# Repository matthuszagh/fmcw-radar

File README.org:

This repo has been moved to [[https://github.com/matthuszagh/fmcw][fmcw]] to support git-lfs (public forks do not support LFS).

* About
:PROPERTIES:
:ID:       20ff1c28-cfc6-4280-8501-83314fee390d
:END:
This repo includes the custom PCBs and PC control software necessary
to build and operate a 6GHz FMCW radar. It also includes a number of
other useful additions, such as RF and SPICE simulations (in progress)
as well as CAD designs for the horn antennas and PCB cases.

The project is a fork of [[https://github.com/Ttl/fmcw3][Henrik's excellent design]]. Although I've made
a number of [[id:8f78da8c-ec0c-40f3-9b8b-6c1af11f4bb2][significant changes]], most of the main PCB (as of this
writing) is still identical to Henrik's. Despite the fact that Henrik
deserves a large share of the credit for this project, he is in no way
affiliated with this fork.

This project is still in its early stages. In particular, there are a
number of hardware issues that make this version inferior to
Henrik's. These will be fixed in a future version, but I would hold
off building this version until these issues are fixed.

* TODO Capabilites
Briefly mention the radar's capabilities.

* TODO Installation
* TODO Additional hardware
* Modifications from the original
:PROPERTIES:
:ID:       8f78da8c-ec0c-40f3-9b8b-6c1af11f4bb2
:END:
The FPGA code has been completely rewritten and expanded so that
nearly all data processing is now done on the FPGA. This was done
while keeping the same FPGA chip. This allows the fully processed
output to be plotted in realtime and simplifies the data processing
requirements of the host PC code. The FPGA code also includes
automated tests and, in some cases, formal verification.

Because the FPGA responsibilities were expanded, the PC software had
new requirements and had to be rewritten as well. The software is
multithreaded and separates out the task of acquiring data from
plotting it. Additionally, the software and FPGA gateware have been
designed to make the radar easier to debug. For instance, data
processing can be shared in any way between the software and FPGA,
which makes gateware bugs easier to isolate. It's also possible to
request data from the FPGA in any intermediate form.

I completely redid the PCB layout because of the need for a new power
amplifier (note that this introduced at least [[id:0246fbe1-ba4a-4bf6-b551-a896264dea3a][one significant issue]]).

I've added horn antennas that can be built by anyone with access to a
3D printer. There's also a 3D-printable mount to hold the entire
structure.

I've greatly expanded the documentation, which should be useful to
anyone who wants to understand how the radar works in detail.

I've added a number of RF simulations (using [[https://openems.de/start/][OpenEMS]]) and spice
simulations (using [[http://ngspice.sourceforge.net/][Ngspice]]).

Finally, I have plans to multiplex 8 receiver antennas across the 2
receiver channels for better angular resolution. The PCB has already
been built (though is untested), but I haven't yet had the time to
write the FPGA code and software to support it.

* Issues and To-Do
:PROPERTIES:
:ID:       0246fbe1-ba4a-4bf6-b551-a896264dea3a
:END:
The power circuitry that was added to accommodate a new power
amplifier (the original was deprecated) adds noise that shows up in
the final output. Because of this problem, if you're able to track
down the old power amplifier I'd recommend using Henrik's design
instead. My FPGA code and software (at least for now) should be fully
compatible with the original hardware. I intend to fix this problem in
a future version.

I'm currently working on a number of RF simulations that will
eventually lead to a replacement of some of the RF PCB
layout. Currently, I have very limited information on whether these
parts of the PCB actually work the way they should. Areas of focus
include transmission line characteristic impedance, transmission line
to SMA transitions, and replacement of discrete components such as
couplers, attenuators, etc. with the equivalent components etched
directly onto the PCB. Once the RF simulations are complete, I'd like
to prototype these before actually building them into the
radar. Unfortunately, I don't yet have the proper testing equipment
for this (building a VNA is the next project...).

* Contributing
Pull requests and issues welcome. I'm open to suggestions for hardware
modification, although may or may not be able to merge those commits
depending on whether I can test the change.

* TODO Operation
Link blog post.

* TODO Attribution
+ Henrik, of course (see [[id:20ff1c28-cfc6-4280-8501-83314fee390d][About]]).
+ An additional thanks to AlexBdx for finding a way to 3D print horn
  antennas.

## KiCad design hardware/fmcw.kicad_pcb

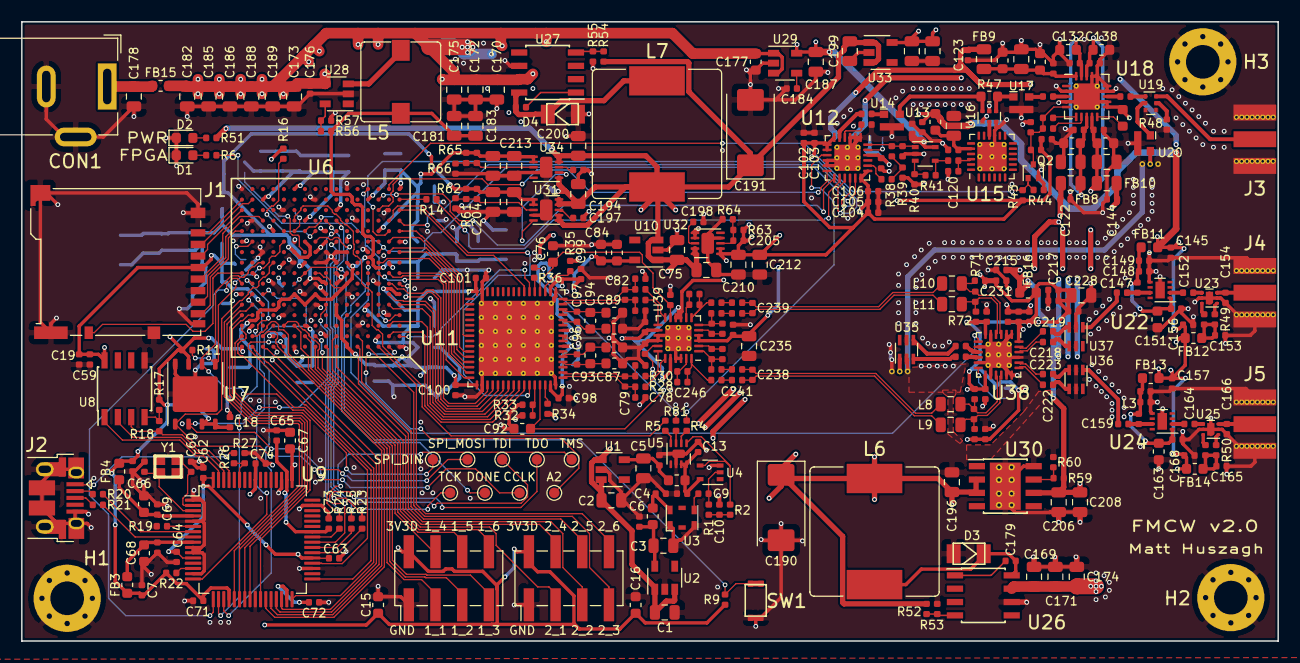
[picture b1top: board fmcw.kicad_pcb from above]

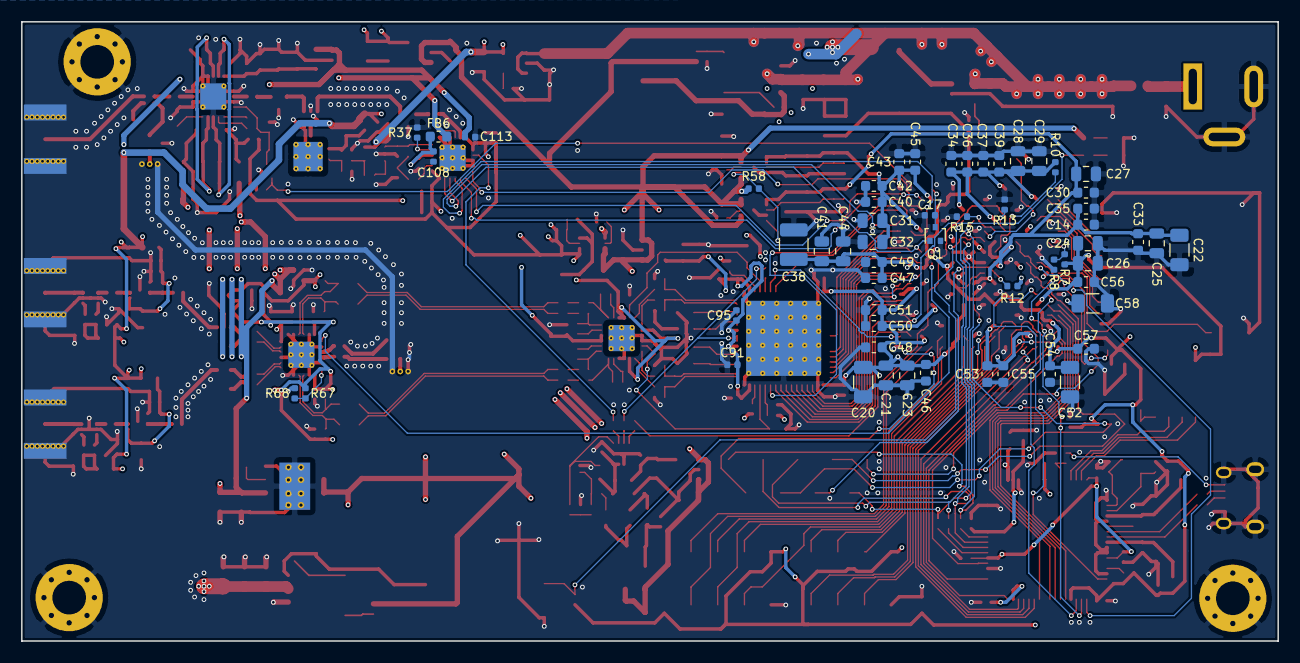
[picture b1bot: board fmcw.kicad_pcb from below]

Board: 4 copper layers, 119.6 x 58.9 mm, 412 parts (57 on the bottom side), 247 nets.

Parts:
C1, C2, C3, C5, C75, C118, C129, C133, C139, C169, C170, C171, C172, C173, C174, C175, C178, C181, C182, C183, C187, C194, C195, C196, C199, C200, C201, C206, C207, C210, C213, C228: 10u; C_0805_2012Metric
C4, C9, C10, C119, C149, C161, C179, C180, C184, C204, C205, C211, C240, C241, C242, C243: 10n; C_0402_1005Metric
C6, C7, C8, C11, C12, C13, C18, C19, C59, C62, C63, C64, C65, C69, C70, C71, C72, C73, C74, C91, C95, C96, C97, C98, C99, C100, C101, C102, C104, C105, C108, C113, C115, C116, C121, C122, C123, C144, C145, C153, C156, C157, C165, C168, C176, C197, C198, C203, C215, C216, C217, C224, C229, C230, C231, C232, C233, C234, C244, C245: 100n; C_0402_1005Metric
C14, C15, C16, C30, C33, C34, C35, C36, C37, C39, C40, C42, C43, C45, C46, C47, C48, C49, C50, C51, C53, C54, C55, C56, C57: 470n; C_0603_1608Metric
C17, C236, C237: DNP; C_0402_1005Metric
C20, C22, C52, C58: 47u; C_1206_3216Metric
C21, C23, C24, C25, C26, C27, C28, C29, C31, C32, C41, C44: 4.7u; C_0805_2012Metric
C38: 100u; C_1210_3225Metric
C60, C61: 15p; C_0402_1005Metric
C66, C67, C68: 4.7u; C_0603_1608Metric
C76, C92, C93, C94, C130, C134, C140: 2.2u; C_0603_1608Metric
C77, C84, C87, C88, C89, C90, C177: 1u; C_0603_1608Metric
C78, C79, C80, C81, C82, C83, C131, C135, C136, C141, C142, C150, C162, C225, C226, C227: 100p; C_0402_1005Metric
C103, C106, C107, C109, C112, C124, C127, C148, C160, C246, C247, C248, C249, C251, C252: 10p; C_0402_1005Metric
C110, C238, C239: 2.2n; C_0402_1005Metric
C114: 51p; C_0402_1005Metric
C120: 68p; C_0402_1005Metric
C128, C132, C137, C138, C151, C163: DNP; C_0603_1608Metric
C147, C152, C159, C164: 18p; C_0402_1005Metric
C154, C166: 0.5p; C_0402_1005Metric
C185, C186, C188, C189, C202, C208, C209, C212, C214, C235: DNP; C_0805_2012Metric
C190, C191: 100u; CP_EIA-7343-31_Kemet-D
C218, C219, C220, C221, C222, C223: 3p; C_0402_1005Metric
CON1: BARREL_JACK; BarrelJack_Wuerth_6941xx301002
D1, D2: Red; LED_0603_1608Metric
D3, D4: SS24FL; SOD-123F
F1, F2: Via-fmcw3-rescue; RF_via
FB1, FB2, FB3, FB4, FB6, FB7, FB11, FB12, FB13, FB14, FB16: BLM18PG181SH1D; L_0603_1608Metric
FB8, FB9, FB10: CIC21P101NE; L_0805_2012Metric
FB15: 74279228600; L_0603_1608Metric
H1, H2, H3: MountingHole_Pad; MountingHole_3.2mm_M3_Pad_Via
J1: SD_Card; microSD_HC_Hirose_DM3BT-DSF-PEJS
J2: USB_B_Micro; USB_Micro-B_Amphenol_10103594-0001LF_Horizontal
J3, J4, J5: SMA; CONSMA003.062
L1, L3: LQW15AN9N9J80D; L_0402_1005Metric
L2, L4: 0.6n; L_0402_1005Metric
L5: 10u; L_Wuerth_WE-PD-Typ-7345
L6, L7: 33u; L_Bourns_SRR1210A
L8, L9, L10, L11: 2.2u; L_0805_2012Metric
P1, P2: CONN_02X04; PinHeader_2x04_P2.54mm_Vertical_SMD
Q1: DNP(RE1C002UN); SOT-416
Q2: RE1C002UN; SOT-416
R1, R2: 470k; R_0402_1005Metric
R4, R5, R14, R23, R24, R25, R81: 33; R_0402_1005Metric
R6, R51: 240; R_0402_1005Metric
R7, R16, R33, R38, R44, R68: DNP; R_0402_1005Metric
R8, R13, R15, R20, R21, R32, R34, R35: 0; R_0402_1005Metric
R9, R10, R11, R26, R40, R41, R42: 4.7k; R_0402_1005Metric
R12, R22: 1k; R_0402_1005Metric
R17, R27, R46, R52, R54: 10k; R_0402_1005Metric
R18: 2.2k; R_0402_1005Metric
R19: 12k; R_0402_1005Metric
R28, R29, R30, R31, R48, R69, R70, R71, R72: 49.9; R_0402_1005Metric
R36: 22; R_0402_1005Metric
R37: 5.49k; R_0402_1005Metric
R39: 3.09k; R_0402_1005Metric
R43: 47k; R_0402_1005Metric
R45, R62: 1.5k; R_0402_1005Metric
R47: 100; R_0603_1608Metric
R49, R50: 100; R_0402_1005Metric
R53: 2.8k; R_0402_1005Metric
R55: 5.11k; R_0402_1005Metric
R56: 4.99k; R_0402_1005Metric
R57: 20k; R_0402_1005Metric
R58: 68k; R_0402_1005Metric
R59: 274k; R_0402_1005Metric
R60: 30.1k; R_0402_1005Metric
R61: 1.87k; R_0402_1005Metric
R63, R65: 3.57k; R_0402_1005Metric
R64, R66: 1.15k; R_0402_1005Metric
R67: 2k; R_0402_1005Metric
R73, R74, R75, R76: 549; R_0402_1005Metric
R77, R78, R79, R80: 8.2k; R_0402_1005Metric
SW1: SW_PUSH; EVP-AWBA2A
TP1, TP2, TP3, TP4, TP5, TP6, TP7, TP8, TP9: TestPoint; TestPoint_Pad_D1.0mm
U1: LP5907MFX-3.3; SOT-23-5
U2: LP5907MFX-1.8; SOT-23-5
U3: KT2520K-T; Oscillator_SMD_Kyocera_2520-6Pin_2.5x2.0mm
U4: NC7SVU04P5X; SOT-353_SC-70-5
U5: NB3N551; DFN-8-1EP_2x2mm_P0.5mm_EP0.8x1.2mm
U6: XC7A15T-FTG256; FTG256
U7: W25Q32JV; DFN-8-1EP_6x5mm_P1.27mm_EP3.4x4.3mm
U8: 93LCxxB; SOIC-8_3.9x4.9mm_P1.27mm
U9: FT2232H; LQFP-64_10x10mm_P0.5mm
U10, U33: LP5907MFX-3.0; SOT-23-5
U11: LTC2292; QFN-64-1EP_9x9mm_P0.5mm_EP7.15x7.15mm_ThermalVias
U12: ADF4158; LFCSP-24-1EP_4x4mm_P0.5mm_EP2.5x2.5mm_ThermalVias
U13: TLV172DCK; SOT-353_SC-70-5
U14: PAT1220-3dB; RF_Attenuator_Susumu_PAT1220
U15: HMC431LP4; QFN-24-1EP_4x4mm_P0.5mm_EP2.8x2.8mm_ThermalVias
U16: PD4859J5050S2HF; Anaren_0805_2012Metric-6
U17: PAT1220-5dB; RF_Attenuator_Susumu_PAT1220
U18: SE5004L; QFN-20-1EP_4x4mm_P0.5mm_EP2.5x2.5mm_ThermalVias
U19: DC4759J5020AHF; Anaren_0805_2012Metric-6
U20: PAT1220-6dB; RF_Attenuator_Susumu_PAT1220
U22, U24: TRF37A73; WSON-8-1EP_2x2mm_P0.5mm_EP0.9x1.6mm
U23, U25: SKY65404; Skyworks_DFN-6-1EP_1.5x1.5mm_P0.5mm_EP0.7x1.2mm
U26, U27: TPS5420D; SOIC-8_3.9x4.9mm_P1.27mm
U28: TPS560200; SOT-23-5
U29: LP2985A-10DBVR; SOT-23-5
U30: TPS7A7001DDA; TI_SO-PowerPAD-8_ThermalVias
U31, U32, U34: TPS7A91; DFN-10-1EP_2.5x2.5mm_P0.5mm_EP1.2x2mm
U35, U36, U37: 5400BL15B050E; Balun_Johanson_5400BL15B050E
U38: ADL5802; LFCSP-24-1EP_4x4mm_P0.5mm_EP2.5x2.5mm_ThermalVias
U39: ADA4940-2; LFCSP-24-1EP_4x4mm_P0.5mm_EP2.5x2.5mm_ThermalVias
Y1: 12MHz; ABM10

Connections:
/1V0: C38.1, C41.1, C44.1, C47.1, C49.1, C52.1, C54.1, C181.1, C183.1, L5.2, R56.1, U6.E10, U6.F7, U6.F9, U6.F11, U6.G6, U6.H9, U6.J6, U6.K9, U6.L8
/1V8: C14.2, C22.1, C25.1, C27.1, C30.1, C33.1, C35.1, C204.1, C207.1, C209.1, R61.1, U6.G8, U6.G10, U6.J10, U6.K11, U6.L10, U31.1, U31.2
/1V8_OSC: C3.1, C6.1, FB1.2, U2.5
/3V0: C116.1, C145.1, C156.1, C157.1, C168.1, C201.1, C202.1, FB7.2, FB11.2, FB12.2, FB13.2, FB14.2, U33.5
/3V3A: C102.1, C103.1, C104.1, C105.1, C106.1, C121.1, C205.1, C210.1, C212.1, C233.1, C234.1, C235.1, R43.1, R45.1, R63.1, U12.6, U12.7, U12.8, U12.18, U12.19, U32.1, U32.2, U39.3, U39.4, U39.9, U39.10, U39.14, U39.20
/3V3D: C7.1, C8.1, C15.1, C16.1, C18.2, C19.1, C20.1, C21.1, C23.1, C24.1, C26.1, C28.1, C29.1, C31.1, C32.1, C34.1, C36.1, C37.1, C39.1, C40.1, C42.1, C43.1, C45.1, C46.1, C48.1, C50.1, C51.1, C53.1, C55.1, C56.1, C57.1, C58.1, C59.1, C65.2, C71.1, C72.1, C73.1, C74.1, C100.1, C101.1, C211.1, C213.1, C214.1, FB3.2, FB4.1, J1.4, P1.2, P2.2, R7.1, R9.1, R10.1, R11.1, R12.1, R16.1, R17.1, R22.2, R65.1, U6.A6, U6.A16, U6.B3, U6.B13, U6.C10, U6.D7, U6.E4, U6.E7, U6.E14, U6.F1, U6.H15, U6.J2, U6.J12, U6.L6, U6.L16, U6.M3, U6.M13, U6.N10, U6.P7, U6.R4, U6.R14, U6.T1, U6.T11, U7.3, U7.7, U7.8, U8.8, U9.20, U9.31, U9.42, U9.50, U9.56, U11.32, U11.49, U34.1, U34.2
/3V3_INV: C5.1, C12.1, FB2.2, U1.5
/3V6: C1.1, C2.1, C75.1, C191.1, C194.1, C195.1, C199.1, C200.1, L7.2, R51.1, R54.1, R58.1, U1.1, U1.3, U2.1, U2.3, U10.1, U10.3, U31.6, U31.7, U31.9, U31.10, U32.6, U32.7, U32.9, U32.10, U33.1, U33.3, U34.6, U34.9, U34.10
/5V: C113.1, C122.1, C123.1, C144.1, C206.1, C208.1, C215.2, FB6.2, FB8.2, FB9.2, FB10.1, FB16.2, R59.1, U30.6
/10V: C115.2, C187.1, U13.5, U29.5
/ADC1+: R31.2, U39.13
/ADC1-: R29.2, U39.12
/ADC2+: R30.2, U39.18
/ADC2-: R28.2, U39.19
/ADC_CE: U6.R3, U12.13
/ADC_REF: R36.2, R81.1, U11.8, U11.9
/ADC_VCM1: C92.2, C244.1, U11.61, U39.17
/ADC_VCM2: C76.1, C245.1, U11.20, U39.11
/ADF_CLK: R14.2, U12.14
/ADF_DATA: U6.M2, U12.15
/ADF_LE: U6.N1, U12.16
/ADF_MUXOUT: Q1.1, U6.K3, U12.17
/ADF_REF: R4.1, U12.9
/ADF_TXDATA: U6.P3, U12.12
/FPGA_REF: R5.1, U6.N11
/LO: F1.1, F2.1, U20.2, U35.1
/MIX_ENBL: U6.J4, U38.7
/PA_OFF: Q2.1, R43.2, R44.1, U6.T2
/RF1: C147.2, U37.1
/RF2: C159.2, U36.1
/fpga/ADC_OE1: U6.B2, U11.58
/fpga/ADC_OE2: U6.P1, U11.23
/fpga/ADC_SHDN1: U6.B1, U11.22
/fpga/ADC_SHDN2: U6.N2, U11.59
/fpga/ADF_DONE: C17.1, Q1.3, U6.T4
/fpga/CARD_DETECT: J1.10, U6.H16
/fpga/CCLK: TP8.1, U6.E8, U7.6
/fpga/CLKOUT: U6.A15, U9.32
/fpga/D0: U6.L2, U11.43
/fpga/D1: U6.K2, U11.44
/fpga/D2: U6.K1, U11.45
/fpga/D3: U6.J3, U11.46
/fpga/D4: U6.H1, U11.47
/fpga/D5: U6.H2, U11.48
/fpga/D6: U6.H3, U11.51
/fpga/D7: U6.G2, U11.52
/fpga/D8: U6.G1, U11.53
/fpga/D9: U6.F2, U11.54
/fpga/D10: U6.E1, U11.55
/fpga/D11: U6.E2, U11.56
/fpga/EXT1_1: P1.3, U6.C11
/fpga/EXT1_2: P1.5, U6.B10
/fpga/EXT1_3: P1.7, U6.A9
/fpga/EXT1_4: P1.4, U6.C12
/fpga/EXT1_5: P1.6, U6.B9
/fpga/EXT1_6: P1.8, U6.A8
/fpga/EXT2_1: P2.3, U6.B7
/fpga/EXT2_2: P2.5, U6.A5
/fpga/EXT2_3: P2.7, U6.A4
/fpga/EXT2_4: P2.4, U6.A7
/fpga/EXT2_5: P2.6, U6.B5
/fpga/EXT2_6: P2.8, U6.A3
/fpga/FT_D0: U6.F15, U9.16
/fpga/FT_D1: U6.G16, U9.17
/fpga/FT_D2: U6.G15, U9.18
/fpga/FT_D3: U6.F14, U9.19
/fpga/FT_D4: U6.E16, U9.21
/fpga/FT_D5: U6.E15, U9.22
/fpga/FT_D6: U6.D16, U9.23
/fpga/FT_D7: U6.D15, U9.24
/fpga/FT_SUSPEND: U6.C16, U9.36
/fpga/INIT_B: R10.2, U6.K10
/fpga/LED: R6.1, U6.D1
/fpga/M0: R16.2, U6.M9
/fpga/M1: R15.1, U6.M10
/fpga/M2: R13.1, U6.M11
/fpga/OE#: U6.A12, U9.33
/fpga/OF1: U6.C2, U11.57
/fpga/OF2: U6.M1, U11.40
/fpga/PROGRAM_B: R9.2, SW1.1, U6.L9
/fpga/RD#: U6.B14, U9.28
/fpga/RXF#: U6.B16, U9.26
/fpga/SD_CLK: J1.5, U6.N14
/fpga/SD_CMD: J1.3, U6.P16
/fpga/SD_DAT0: J1.7, U6.N16
/fpga/SD_DAT1: J1.8, U6.M16
/fpga/SD_DAT2: J1.1, U6.R16
/fpga/SD_DAT3: J1.2, U6.R15
/fpga/SIWUA: U6.A13, U9.30
/fpga/SPI_CS: R11.2, U6.L12, U7.1
/fpga/SPI_DIN: TP1.1, U6.J14, U7.2
/fpga/SPI_MOSI: TP2.1, U6.J13, U7.5
/fpga/TCK: R23.1, TP6.1, U6.L7
/fpga/TDI: R25.1, TP3.1, U6.N7
/fpga/TDO: TP4.1, U6.N8, U9.40
/fpga/TMS: R24.1, TP5.1, U6.M7
/fpga/TXE#: U6.B15, U9.27
/fpga/WR: U6.A14, U9.29
/fpga/adc/3V0: R32.1, R34.2, R35.2
/fpga/adc/AINA+: C78.2, C79.1, R28.1, U11.1
/fpga/adc/AINA-: C79.2, C80.1, R30.1, U11.2
/fpga/adc/AINB+: C81.2, C82.1, R29.1, U11.16
/fpga/adc/AINB-: C82.2, C83.1, R31.1, U11.15
/fpga/usb/1V8: C62.1, C63.1, C64.1, C67.1, U9.12, U9.37, U9.49, U9.64
/fpga/usb/DO: R17.2, R18.1, U8.4
/fpga/usb/EECLK: U8.2, U9.62
/fpga/usb/EECS: U8.1, U9.63
/fpga/usb/EEDATA: R18.2, U8.3, U9.61
/fpga/usb/USBDM: J2.2, R20.2
/fpga/usb/USBDP: J2.3, R21.2
/fpga/usb/USB_5V: J2.1, R26.1
/if/IF1+: C237.2, L11.1, R72.2, U38.4
/if/IF1-: C237.1, L10.1, R71.1, U38.3
/if/IF1a+: C239.2, C243.2, L11.2
/if/IF1a-: C239.1, C242.2, L10.2
/if/IF1b+: C243.1, R76.2
/if/IF1b-: C242.1, R75.2
/if/IF2+: C236.2, L9.1, R70.2, U38.16
/if/IF2-: C236.1, L8.1, R69.1, U38.15
/if/IF2a+: C238.2, C241.2, L9.2
/if/IF2a-: C238.1, C240.2, L8.2
/if/IF2b+: C241.1, R74.2
/if/IF2b-: C240.1, R73.2
/mixer/5VF: C216.2, C217.2, C224.2, C225.2, C226.2, C227.2, C228.2, C229.2, C230.2, C231.2, C232.2, FB16.1, R67.1, R69.2, R70.1, R71.2, R72.1, U38.6, U38.13, U38.24
/mixer/LOIa+: C220.2, U35.4
/mixer/LOIa-: C221.2, U35.3
/mixer/LOIb+: C220.1, U38.9
/mixer/LOIb-: C221.1, U38.10
/mixer/RF1a+: C219.2, U37.3
/mixer/RF1a-: C218.2, U37.4
/mixer/RF1b+: C219.1, U38.23
/mixer/RF1b-: C218.1, U38.22
/mixer/RF2a+: C223.2, U36.3
/mixer/RF2a-: C222.2, U36.4
/mixer/RF2b+: C223.1, U38.20
/mixer/RF2b-: C222.1, U38.19
/power/5V6: C190.1, C196.1, L6.2, R52.1, U30.2, U30.3
/power/12V: C169.1, C170.1, C171.1, C172.1, C173.1, C174.1, C175.1, C176.1, C177.1, C182.1, C185.1, C186.1, C188.1, C189.1, FB15.1, U26.7, U27.7, U28.4, U29.1, U29.3
GND: C1.2, C2.2, C3.2, C4.1, C5.2, C6.2, C7.2, C8.2, C10.1, C11.1, C12.2, C13.1, C14.1, C15.2, C16.2, C17.2, C18.1, C19.2, C20.2, C21.2, C22.2, C23.2, C24.2, C25.2, C26.2, C27.2, C28.2, C29.2, C30.2, C31.2, C32.2, C33.2, C34.2, C35.2, C36.2, C37.2, C38.2, C39.2, C40.2, C41.2, C42.2, C43.2, C44.2, C45.2, C46.2, C47.2, C48.2, C49.2, C50.2, C51.2, C52.2, C53.2, C54.2, C55.2, C56.2, C57.2, C58.2, C59.2, C60.2, C61.2, C62.2, C63.2, C64.2, C65.1, C66.2, C67.2, C68.2, C69.2, C70.2, C71.2, C72.2, C73.2, C74.2, C75.2, C76.2, C77.2, C78.1, C80.2, C81.1, C83.2, C84.2, C87.2, C88.2, C89.2, C90.2, C91.2, C92.1, C95.2, C98.2, C99.2, C100.2, C101.2, C102.2, C103.2, C104.2, C105.2, C106.2, C107.1, C108.2, C109.2, C113.2, C114.2, C115.1, C116.2, C118.1, C119.1, C120.2, C121.2, C122.2, C123.2, C128.2, C129.2, C130.2, C131.2, C132.1, C133.1, C134.1, C135.1, C136.1, C137.2, C138.1, C139.1, C140.1, C141.1, C142.1, C144.2, C145.2, C148.2, C149.2, C150.2, C151.2, C153.2, C154.2, C156.2, C157.2, C160.2, C161.2, C162.2, C163.2, C165.2, C166.2, C168.2, C169.2, C170.2, C171.2, C172.2, C173.2, C174.2, C175.2, C176.2, C177.2, C178.2, C181.2, C182.2, C183.2, C184.2, C185.2, C186.2, C187.2, C188.2, C189.2, C190.2, C191.2, C194.2, C195.2, C196.2, C197.2, C198.2, C199.2, C200.2, C201.2, C202.2, C203.2, C206.2, C207.2, C208.2, C209.2, C210.2, C212.2, C213.2, C214.2, C215.1, C216.1, C217.1, C224.1, C225.1, C226.1, C227.1, C228.1, C229.1, C230.1, C231.1, C232.1, C233.2, C234.2, C235.2, C244.2, C245.2, CON1.2, CON1.3, D1.1, D2.1, D3.2, D4.2, F1.2, F2.2, H1.1, H2.1, H3.1, J1.6, J1.9, J1.11, J2.5, J2.6, J3.2, J4.2, J5.2, P1.1, P2.1, Q1.2, Q2.2, R8.2, R13.2, R15.2, R19.2, R27.2, R33.2, R37.2, R39.1, R40.2, R44.2, R46.2, R48.1, R53.2, R55.2, R57.2, R60.2, R62.2, R64.2, R66.2, R68.2, SW1.2, U1.2, U2.2, U3.1, U3.3, U4.3, U5.6, U5.9, U6.A1, U6.A11, U6.B8, U6.C5, U6.C15, U6.D2, U6.D12, U6.E9, U6.F6, U6.F8, U6.F10, U6.F16, U6.G3, U6.G7, U6.G9, U6.G13, U6.H6, U6.H7, U6.J7, U6.J8, U6.J9, U6.J11, U6.K4, U6.K6, U6.K7, U6.K8, U6.K14, U6.L1, U6.L11, U6.M8, U6.N5, U6.N15, U6.P2, U6.P12, U6.R9, U6.T6, U6.T16, U7.4, U7.9, U8.5, U9.1, U9.5, U9.10, U9.11, U9.13, U9.15, U9.25, U9.35, U9.47, U9.51, U10.2, U11.17, U11.31, U11.50, U11.64, U11.65, U12.1, U12.2, U12.3, U12.10, U12.11, U12.25, U13.2, U14.3, U15.15, U15.25, U16.1, U16.3, U16.5, U17.3, U18.2, U18.4, U18.11, U18.12, U18.14, U18.15, U18.16, U18.17, U18.21, U19.3, U19.4, U20.3, U22.5, U22.9, U23.2, U23.5, U23.7, U24.5, U24.9, U25.2, U25.5, U25.7, U26.6, U27.6, U28.2, U29.2, U30.8, U30.9, U31.4, U31.11, U32.4, U32.11, U33.2, U34.4, U34.11, U35.2, U35.5, U36.2, U36.5, U37.2, U37.5, U38.1, U38.2, U38.5, U38.8, U38.11, U38.14, U38.17, U38.18, U38.21, U38.25, U39.15, U39.16, U39.21, U39.22, U39.25
unnamed: C4.2, FB1.1, U3.6
unnamed: C9.1, R1.2, U4.2
unnamed: C9.2, U3.4
unnamed: C10.2, R1.1, R2.2
unnamed: C11.2, C13.2, FB2.1, U4.5, U5.7, U5.8
unnamed: C60.1, U9.2, Y1.1
unnamed: C61.1, U9.3, Y1.3
unnamed: C66.1, C69.1, FB4.2, U9.4
unnamed: C68.1, C70.1, FB3.1, U9.9
unnamed: C77.1, C84.1, C91.1, C95.1, C98.1, C99.1, U10.5, U11.7, U11.10, U11.18, U11.63
unnamed: C87.1, C93.1, C96.1, U11.3, U11.4
unnamed: C88.1, C93.2, C96.2, U11.5, U11.6
unnamed: C89.1, C94.1, C97.1, U11.13, U11.14
unnamed: C90.1, C94.2, C97.2, U11.11, U11.12
unnamed: C107.2, U12.4
unnamed: C108.1, C109.1, FB6.1, U12.22
unnamed: C110.1, C114.1, U12.24, U13.1
unnamed: C110.2, R38.1, R39.2
unnamed: C112.1, U14.1
unnamed: C112.2, U12.5
unnamed: C118.2, C119.2, FB7.1, U15.20
unnamed: C120.1, R42.1, U15.22
unnamed: C124.1, U18.7
unnamed: C124.2, C127.2, Q2.3, R45.2, R46.1, U18.5
unnamed: C127.1, U18.6
unnamed: C128.1, C129.1, C130.1, C131.1, FB9.1, U18.20
unnamed: C132.2, C133.2, C134.2, C135.2, C136.2, FB8.1, U18.8, U18.19
unnamed: C137.1, U18.10
unnamed: C138.2, C139.2, C140.2, C141.2, C142.2, FB10.2, U18.9, U18.18
unnamed: C147.1, L1.1, U22.7
unnamed: C148.1, C149.1, C150.1, C151.1, FB11.1, L1.2, U22.1
unnamed: C152.1, U23.4
unnamed: C152.2, U22.2
unnamed: C153.1, FB12.1, L2.2, R49.2
unnamed: C154.1, J4.1, U23.3
unnamed: C159.1, L3.1, U24.7
unnamed: C160.1, C161.1, C162.1, C163.1, FB13.1, L3.2, U24.1
unnamed: C164.1, U25.4
unnamed: C164.2, U24.2
unnamed: C165.1, FB14.1, L4.2, R50.2
unnamed: C166.1, J5.1, U25.3
unnamed: C178.1, CON1.1, FB15.2
unnamed: C179.1, D3.1, L6.1, U26.8
unnamed: C179.2, U26.1
unnamed: C180.1, D4.1, L7.1, U27.8
unnamed: C180.2, U27.1
unnamed: C184.1, U29.4
unnamed: C197.1, U31.8
unnamed: C198.1, U32.8
unnamed: C203.1, U34.8
unnamed: C204.2, R61.2, R62.1, U31.3
unnamed: C205.2, R63.2, R64.1, U32.3
unnamed: C211.2, R65.2, R66.1, U34.3
unnamed: C246.1, R78.1, U39.23
unnamed: C246.2, R74.1, R78.2, U39.24
unnamed: C247.1, R80.1, U39.5
unnamed: C247.2, R76.1, R80.2, U39.6
unnamed: C248.1, R73.1, R77.1, U39.1
unnamed: C248.2, R77.2, U39.2
unnamed: C249.1, R75.1, R79.1, U39.7
unnamed: C249.2, R79.2, U39.8
unnamed: C251.1, U18.3
unnamed: C251.2, U17.2
unnamed: C252.1, U19.1
unnamed: C252.2, U18.13
unnamed: D1.2, R6.2
unnamed: D2.2, R51.2
unnamed: J3.1, U19.6
unnamed: L2.1, U23.6
unnamed: L4.1, U25.6
unnamed: L5.1, U28.3
unnamed: R2.1, U4.4, U5.1
unnamed: R4.2, U5.2
unnamed: R5.2, U5.4
unnamed: R7.2, R8.1, U6.L15
unnamed: R12.2, TP7.1, U6.H10
unnamed: R14.1, U6.R1
unnamed: R19.1, U9.6
unnamed: R20.1, U9.7
unnamed: R21.1, U9.8
unnamed: R22.1, U9.14
unnamed: R23.2, U9.38
unnamed: R24.2, U9.41
unnamed: R25.2, U9.39
unnamed: R26.2, R27.1, U9.59
unnamed: R32.2, R33.1, U11.60
unnamed: R34.1, U11.62
unnamed: R35.1, U11.19
unnamed: R36.1, U11.21
unnamed: R37.1, U12.23
unnamed: R38.2, U12.20
unnamed: R40.1, R41.2, U13.3
unnamed: R41.1, R42.2, U13.4
unnamed: R47.1, U16.4, U17.1
unnamed: R47.2, U14.2, U16.6
unnamed: R48.2, U19.5
unnamed: R49.1, U23.1
unnamed: R50.1, U25.1
unnamed: R52.2, R53.1, U26.4
unnamed: R54.2, R55.1, U27.4
unnamed: R56.2, R57.1, U28.5
unnamed: R58.2, U31.5, U34.7
unnamed: R59.2, R60.1, U30.7
unnamed: R67.2, R68.1, U38.12
unnamed: R81.2, U5.3
unnamed: TP9.1, U6.A2
unnamed: U15.16, U16.2
unnamed: U19.2, U20.1

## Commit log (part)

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2017-09-27 Fix FPGA programming resistor connections
    M[2:0] were wired incorrectly when I ordered the board. For programming from SPI
    memory M[2:0] should be "001", but I had them wired backwards as "100". I fixed
    it with one jump wire, but here is a proper fix for anyone looking to reproduce
    the design.
2017-09-28 Update blog post link
2018-10-06 Current working version.
2018-10-10 Dropped the 3 from the end of the project name.
2018-12-11 Modularized LaTeX documentation.
2018-12-18 Adjusted power supply for new power amplifier.
2018-12-20 Documentation for TPS5420D buck converter.
2018-12-26 Made some modifications to the power hardware.
2018-12-30 Improved top level documentation.
2019-01-04 Added MFNs to components.
2019-01-08 Improved documentation and added schematics to default libraries.
2019-01-08 Improved tx sheet and corresponding documentation.
2019-01-09 Improved documentation and parts of the schematic.
2019-01-11 Changed components to official libs.
2019-01-12 Finished design, began routing.
2019-01-13 Placed most major components.
2019-01-14 Completed clock placement and routing.
2019-01-15 Place/route for ft2232h.
2019-01-15 Fixed transmission line width.
2019-01-15 Added test points.
2019-01-16 Placed/routed all FPGA external components.
2019-01-16 Better MFNs for RF DC blocking caps.
2019-01-16 Completed transmitter placement/routing.
2019-01-17 Completed receivers.
2019-01-17 Finished placing.
2019-01-17 Passes DRC.
2019-01-17 Completed power plane.
2019-01-17 Replaced relevant footprints for thermal via variety.
2019-01-18 Improved silkscreen appearance.
2019-01-23 Documentation changes.
2019-01-24 Add patch antenna.
2019-01-24 Documentation improvements and spice simulations.
2019-02-02 Filter FPGA code.
2019-02-02 Place ADC logic directly in top level module.
2019-02-10 Finish FPGA code.
2019-02-24 Added Makefiles to facilitate running code. Reorganized code.
2019-02-24 Add buffer amp for power amp reference voltage.
2019-02-27 Improve PCB.
2019-02-28 Add RF antenna switch.
2019-08-10 Unoptimized, working FFT
    This commit is a huge abuse of git, I know...
2019-09-27 Huge, messy commit before I begin replacing FPGA code
2019-10-01 Add beamforming doc
2019-10-01 Move FPGA code to dedicated subdirectories
    This project will have several different
    configurations. There will be at least 2: (1) just
    to calculate range and (2) calculate range and
    angle data.
2019-10-01 Remove test signals from FPGA code
    This commit simply cleans up the FPGA to act as a
    reference point from which to test.
2019-10-02 Move tap address update in FIR
2019-10-02 Source some cores from libdigital repo
    Previously, I had been copying the relevant files
    from libdigital to this project. Therefore, any
    changes needed to be implemented twice. Instead,
    they should be modified once in the libdigital
    repo and then included here.
2019-10-03 Fix FFT data sent to host
2019-10-03 Minor change
2019-10-03 Add C program for reading raw binary data
    This accepts a header+payload format where the
    header is any 4 or 8 bits and the payload can
    consist of any bit sequence corresponding to any
    sequence of data points (they do not need to be
    byte-aligned). The total header+payload must be
    byte-aligned.
2019-10-04 Eliminate most errors related to missed or erroneous reads
    There still might be a few errors here, but not many.
2019-10-04 Add linker flags to Makefile for reading bytes from fmcw board
2019-10-04 Add code to compute FFT magnitude and generate file
2019-10-04 Update Python plotting
2019-10-04 Add files to gitignore
2019-10-04 Add nix shell file for reproducible environments
2019-10-05 read_bytes: Add numerous payloads for different output data
2019-10-05 Fix FFT power computation when reading bytes
2019-10-05 Add functions to plot file
2019-10-05 Use 40 clk input for all 4 derived clocks
    This also requires a synchronization register at
    the output.
2019-10-06 Add facility to measure error detection method efficacy
2019-10-06 Replace adc.v with ltc2292.v
    This uses a dedicated libdigital interface in
    place of the old adc.v interface.
2019-10-12 Update shell nix file
2019-10-16 Remove adc module from makefile
2019-10-16 Remove Makefile include file and make libdigital_path enviro variable
2019-10-16 Make makefile less verbose
    In particular this uses commands to automatically
    find source files.
2019-10-16 Fix ltc2292 instantiation syntax error
2019-10-16 Set libdigital_path from env in vivado synth script
2019-10-16 Add missing verilog includes to Makefile
2019-10-16 Use separate PLL's for onboard logic clocks and FT2232H clocks
2019-10-16 Use new FT245 module for sending data to host PC
    This has a number of advantages over the previous
    implementation. Because it uses an asynchronous
    FIFO internally, CDC issues are no longer a
    concern. This also means you can change the source
    of transmission data (e.g. betwen FIR, FFT, etc.)
    without changing the logic. All you need to change
2019-10-16 Current plotting and reading implementation
2019-10-16 Only enable ADC when in use
2019-11-05 reorganize project and create synthesizable top level
2019-11-05 program FPGA from top-level makefile
2019-11-06 nix shell: add option to compile everything with musl
2019-11-06 add plot data program
    Takes the raw byte reads and extracts packet data.
2019-11-06 fix bit extraction function
2019-11-06 add makefile lint
2019-11-07 data processing: add parity check and dvalid function
2019-11-08 top verilog: replace ram with fifo
    Between filter and fft
2019-11-08 improve data pc data processing
    Previously, the algorithm to post process data
    would discard data if it detected an error and
    keep reading. However, this was done in such a way
    that future reads would be misaligned and it would
    throw everything out until another error occured
    which realigned it. This fixes that alignment
2019-11-11 fix fft no output data issue
2019-11-11 fft now sends all data (real + imag + ctr)
2019-11-11 update read to combine fft real and imaginary during read
2019-11-11 create separate file for each timestep and remove parity check
2019-11-12 fix add_byte_to_word
2019-11-12 read and process data in real time simultaneously
2019-11-13 live plotting works
2019-11-17 read: only write first half of fft
2019-11-17 modify plot to only plot first half of fft
2019-11-17 interact with radar as normal user
    This requires proper udev setup but is useful
    since it allows interaction with the board as a
    normal user. One example where this comes in handy
    is when debugging the code to read from the radar.
2019-11-17 set debug in top level makefile
2019-11-17 use kaiser window before fft
2019-11-21 change read filename to fmcw
2019-11-21 use pll_sync_ctr for ft245
    This appears to fix the bug where the PC code was
    intermittently missing many reads.
2019-11-21 generalize top-level control logic
    This makes it easier to switch between sending
    fully-processed data and data in some intermediate
    state.
2019-11-21 add top-level test
2019-11-21 add pc executable to top-level ignored files
2019-11-22 gateware: fix ft245 data width
2019-11-22 move spice sims
2019-11-26 software multithreading support
2019-12-06 gateware: add delay to limit data loss
2019-12-06 gateware: increase FT245 write fifo depth
2019-12-06 software: use goto for memory cleanup
2019-12-06 software: add interpolation and thread for user input
2019-12-06 software: fix linear interpolation
2019-12-06 software: more friendly user input
2019-12-08 replace delay state with ft245 state
    Wait for the FT245 write FIFO buffer to signal it's empty before
    starting the next sequence. Previously, we used a delay counter. The
    new implementation is wastes less time, uses fewer resources (no
    longer requires the counter register) and is more flexible (does not
    require adapting for different lengths of data).
2019-12-11 software: communicate with python as subprocess
    This is a major overhaul of the previous PC code configuration. There
    are 2 major changes:
    1. Allow any breakdown of processing between PC and FPGA. The PC can
    also optionally skip steps (the FPGA currently cannot).
    2. Communicate with the Python plotting code as a subprocess of the C
    code. The python process is started as an unnamed pipe and data is
2019-12-11 gateware: improve top module comment formatting
2019-12-11 gateware: add test capability to simulate sending commands to FPGA
2019-12-11 software: fix FFT hist plotting and other bug fixes
2019-12-11 gateware: wait for first ramp before commencing any processing
2019-12-11 gateware: use ramp synchronization
2019-12-12 gateware: fix window module
2019-12-12 gateware: move source files
2019-12-12 software: add background subtract
2019-12-12 software: add subtract last option
2019-12-19 cad: add antenna mount
2019-12-19 add apache license in accordance with forked repo
2019-12-19 gateware: sync led with power amplifier
    Data is transmitted too infrequently to the PC to be visible via the
    LED.
2020-01-03 pcb: connect ADC reference to voltage supply rail
2020-01-07 create operation document
2020-01-07 documentation: phase-detector description
2020-01-18 documentation: add note to reader about detailed sections
2020-01-22 doc: fpga block diagram
2020-01-22 doc: add description to FPGA block diagram
2020-01-23 doc: add fir filter high-level description
2020-01-23 doc: clarify 1MHz cutoff for FIR filter
2020-01-23 doc: windowing and detailed explanation of spectral leakage
2020-01-23 doc: detailed explanation of windowing
2020-01-24 doc: move simulation sections after FPGA and software
2020-01-24 doc: window function implementation
2020-01-24 doc: FIR implementation
2020-01-28 doc: use gettikzxy for main block diagram
2020-01-28 doc: improve transmitter high-level description
2020-01-28 doc: add FFT schematic
2020-01-28 doc: add software block diagram
2020-01-28 doc: improve software diagram and extend description
2020-01-28 doc: receiver block diagram
2020-01-31 doc: add receiver top level description and differential amp
2020-01-31 doc: range equation derivation
2020-01-31 doc: minimum detectable power and max range
2020-01-31 doc: minimum range
2020-01-31 doc: rename receiver section to noise figure and gain
2020-01-31 doc: software error detection
2020-01-31 doc: remove unused old documentation
2020-02-01 doc: remove angle calculation section
    We're only computing the distance in this iteration, so we can leave
    this out until the angle calculation is implemented.
2020-02-01 doc: remove unused spice simulations section
2020-02-01 doc: improve phase detector diagram
2020-02-01 doc: add digital interface diagram
2020-02-01 doc: rename FPGA to FPGA gateware
    Distinguishes from FPGA section in digital interface
2020-02-01 doc: digitization diagram add usb data rate
2020-02-02 doc: adc high-level description
2020-02-02 doc: fpga high-level description
2020-02-02 doc: ft2232h high-level description
2020-02-02 doc: add note about omitted adc 2nd channel
2020-02-02 readme: add issues section
2020-02-02 readme: add contributing section
2020-02-03 readme: add note about ongoing RF simulations
2020-02-03 remove old gateware
2020-02-03 copy gateware over from libdigital repo
    This reduces modularity somewhat but makes this project more
    self-contained. Additionally, that repo was a mess.
2020-02-03 remove libdigital dependency
2020-02-03 remove old software files
2020-02-03 move main pcb hardware to boards+version subdirectory
2020-02-04 add if amplifier simulation
2020-02-06 move doc to blog
2020-02-21 readme: modify attribution and warning
2020-02-21 readme: only link to henrik's github repo
2020-02-21 add horn antenna openems simulation
2020-02-23 add dual_ff formal verification
2020-02-23 add pll sync ctr formal verification
2020-02-24 fix fir bug related to improper normalization factor
2020-02-24 add plot color
2020-02-24 add y-axis values
